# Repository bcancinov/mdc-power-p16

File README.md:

# mdc-power-p16
Modular Detector Controller Power 16V DC-DC Mezzanine Module

## Overview
12V input to 16V output DC-DC module, 0.5A nominal output, used as one of the `mdc-power-*` bias rails.
Designed for 2 MHz sync operation.
Mezzanine module.

## Power Stage
- Controller: `LT8350S` (`U1`)
  - 4-switch, single-inductor synchronous buck-boost controller (Silent Switcher 2 family).
  - Supports input above/below VOUT, suitable for regulated 16V from 12V input.
  - Silent Switcher 2 architecture for reduced EMI and cleaner switch-node behavior.
  - Single-inductor buck-boost topology simplifies power stage while handling input transients.
- Inductor: `L1` = `3.3uH`
  - Uses the XGL4020 shielded power inductor family (see `docs/xgl4020.pdf`).
  - Shielded construction to reduce radiated EMI and coupling into sensitive nodes.
  - Very low DCR family to reduce copper loss and improve efficiency.
  - Low AC loss construction optimized for high-frequency switching.

## Files
- Schematic: `power_p16.pdf`
- Simulation: `sim/` (LTspice and LTpowerCAD files used for loop and transient checks)

## Board Dimensions
- 44.8 mm x 41.5 mm

## Board Stackup
- 4-layer PCB

## CAD
- Designed using KiCad 9.

## Interface
- Control pins: `EN` (enable) and `PG` / `~PGOOD` (power good).
- Connector: `LSHM-140-04.0-L-DV-A-N-K-TR` (Samtec LSHM series) mezzanine for power and control signals.
  - Common pinout is shared across the 16V, -16V, 6V, and 3.3V variants.
  - Unused output rails are tied to GND on the specific module variant.

## Images
Layout:

3D view:

## License

This hardware design is licensed under the **Creative Commons Attribution-NonCommercial-ShareAlike 4.0 International License** (CC BY-NC-SA 4.0).

You are free to download, modify, and build upon this design for your own research or personal use, provided you give appropriate credit and share your modifications under the exact same license. **Commercial manufacturing or use of these designs is strictly prohibited without explicit permission.**

To view a copy of this license, visit [http://creativecommons.org/licenses/by-nc-sa/4.0/](http://creativecommons.org/licenses/by-nc-sa/4.0/) or see the `LICENSE` file in this repository.

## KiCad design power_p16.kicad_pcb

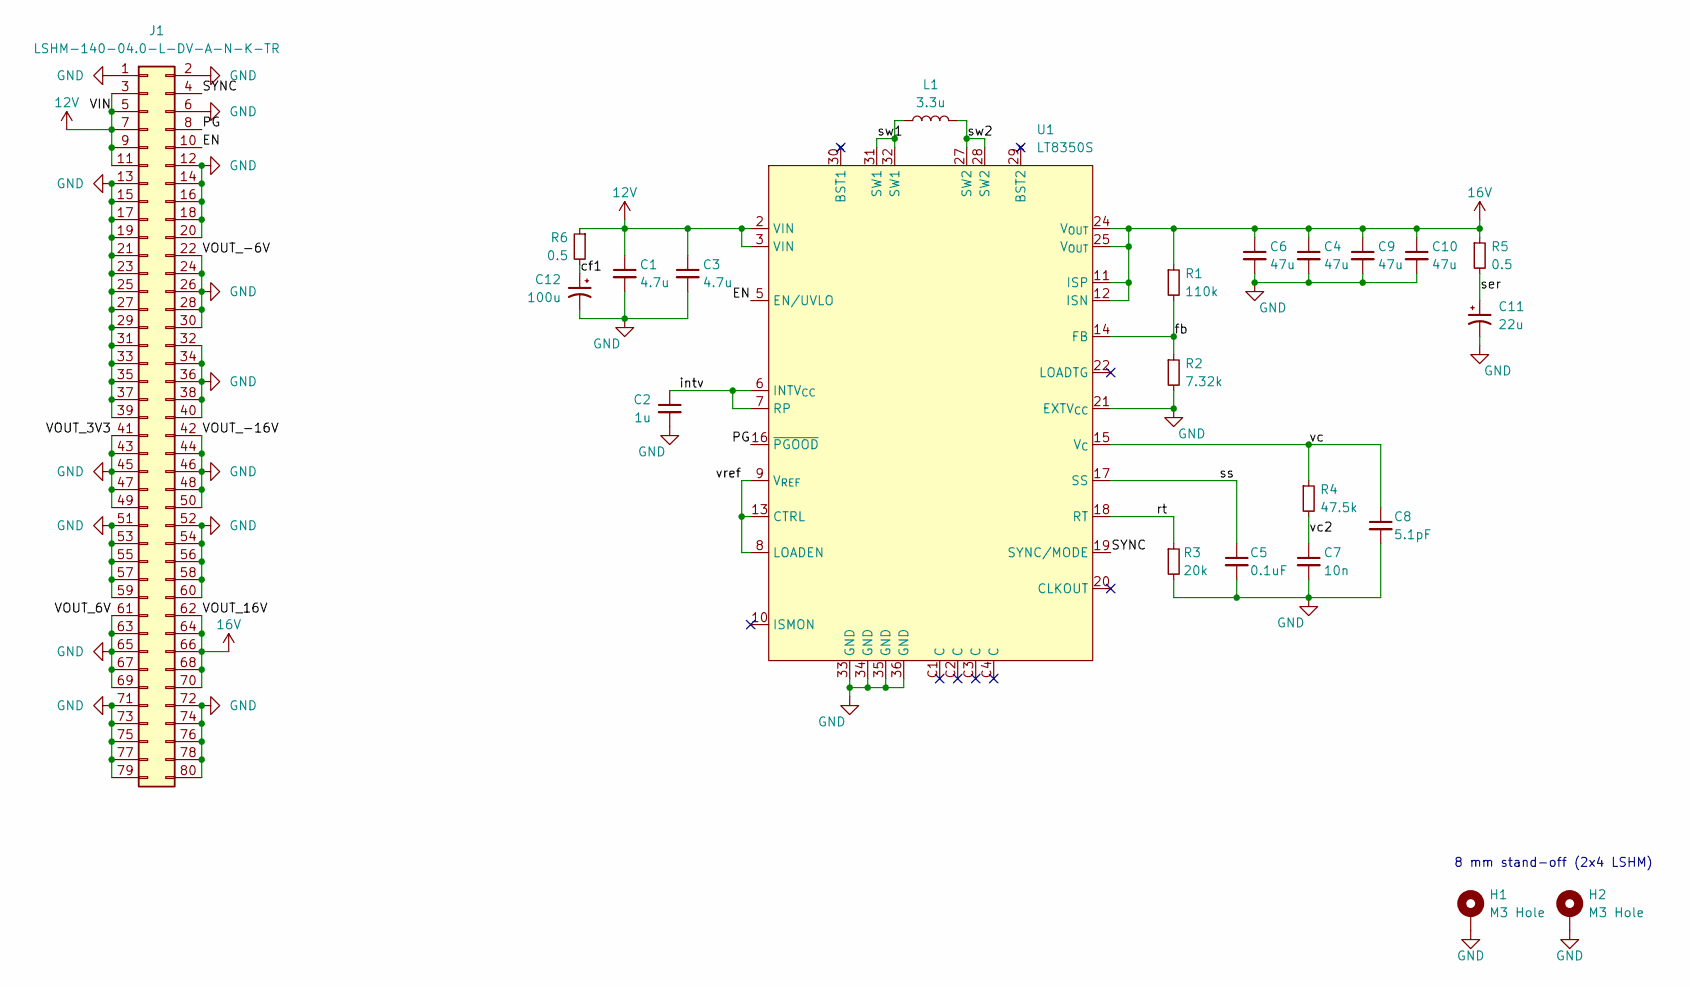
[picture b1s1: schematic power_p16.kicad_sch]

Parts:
C1, C3: 4.7u; C_1210_3225Metric; MPN GCM32ER71H475KA55K
C2: 1u; C_0603_1608Metric; MPN GCM188R71E105KA64D
C4, C6, C9, C10: 47u; C_1210_3225Metric; MPN TMK325ABJ476MM-P
C5: 0.1uF; C_0402_1005Metric; MPN GCM155R71H104KE02J
C7: 10n; C_0603_1608Metric; MPN GRT1885C1E103FA02D
C8: 5.1pF; C_0603_1608Metric; MPN CBR06C519C5GACAUTO
C11: 22u; CP_EIA-7343-20_Kemet-V; MPN T521V226M025ATE040
C12: 100u; T521X; MPN T521X107M025ATE060
H1, H2: M3 Hole; MountingHole_3.2mm_M3_Pad_Via
J1: LSHM-140-04.0-L-DV-A-N-K-TR; SAMTEC_LSHM-140-04.0-L-DV-A-N-K-TR; MPN LSHM-140-04.0-L-DV-A-N-K-TR
L1: 3.3u; XGL4020; MPN XGL4020-332MEC
R1: 110k; R_0603_1608Metric; MPN ERA-3AEB114V
R2: 7.32k; R_0603_1608Metric; MPN ERA-3AEB7321V
R3: 20k; R_0603_1608Metric; MPN CRCW060320K0FKEA
R4: 47.5k; R_0603_1608Metric; MPN CRCW060347K5FKEA
R5, R6: 0.5; R_0603_1608Metric; MPN RCWE0603R500FKEA
U1: LT8350S; MPN LT8350SAV#PBF

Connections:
12V: C1.1, C3.1, J1.3, J1.5, J1.7, J1.9, J1.11, R6.1, U1.2 (VIN), U1.3 (VIN)
16V: C4.1, C6.1, C9.1, C10.1, J1.62, J1.64, J1.66, J1.68, J1.70, R1.1, R5.1, U1.11 (ISP), U1.12 (ISN), U1.24 (V_{OUT}), U1.25 (V_{OUT})
/EN: J1.10, U1.5 (EN/UVLO)
/PG: J1.8, U1.16 (~PGOOD)
/SYNC: J1.4, U1.19 (SYNC/MODE)
/cf1: C12.1, R6.2
/fb: R1.2, R2.1, U1.14 (FB)
/intv: C2.1, U1.6 (INTV_{CC}), U1.7 (RP)
/rt: R3.1, U1.18 (RT)
/ser: C11.1, R5.2
/ss: C5.1, U1.17 (SS)
/sw1: L1.2, U1.31 (SW1), U1.32 (SW1)
/sw2: L1.1, U1.27 (SW2), U1.28 (SW2)
/vc: C8.1, R4.1, U1.15 (V_{C})
/vc2: C7.1, R4.2
/vref: U1.8 (LOADEN), U1.9 (V_{REF}), U1.13 (CTRL)
GND: C1.2, C2.2, C3.2, C4.2, C5.2, C6.2, C7.2, C8.2, C9.2, C10.2, C11.2, C12.2, H1.1, H2.1, J1.1, J1.2, J1.6, J1.12, J1.13, J1.14, J1.15, J1.16, J1.17, J1.18, J1.19, J1.20, J1.21, J1.22, J1.23, J1.24, J1.25, J1.26, J1.27, J1.28, J1.29, J1.30, J1.31, J1.32, J1.33, J1.34, J1.35, J1.36, J1.37, J1.38, J1.39, J1.40, J1.41, J1.42, J1.43, J1.44, J1.45, J1.46, J1.47, J1.48, J1.49, J1.50, J1.51, J1.52, J1.53, J1.54, J1.55, J1.56, J1.57, J1.58, J1.59, J1.60, J1.61, J1.63, J1.65, J1.67, J1.69, J1.71, J1.72, J1.73, J1.74, J1.75, J1.76, J1.77, J1.78, J1.79, J1.80, R2.2, R3.2, U1.21 (EXTV_{CC}), U1.33 (GND), U1.34 (GND), U1.35 (GND), U1.36 (GND)

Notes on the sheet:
8 mm stand-off (2x4 LSHM)

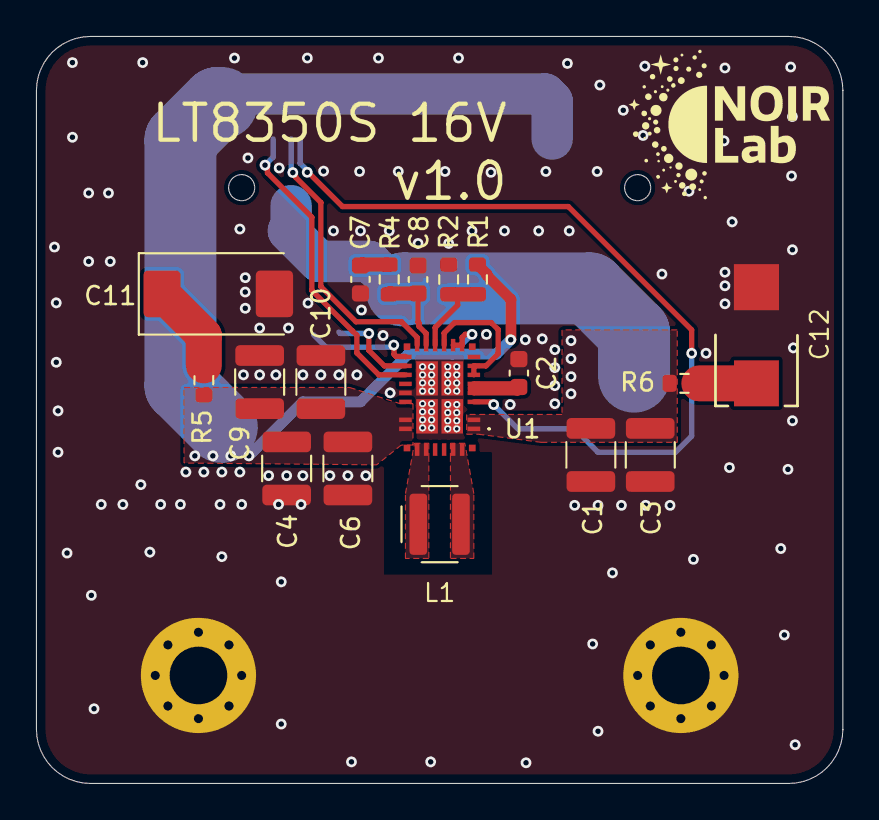
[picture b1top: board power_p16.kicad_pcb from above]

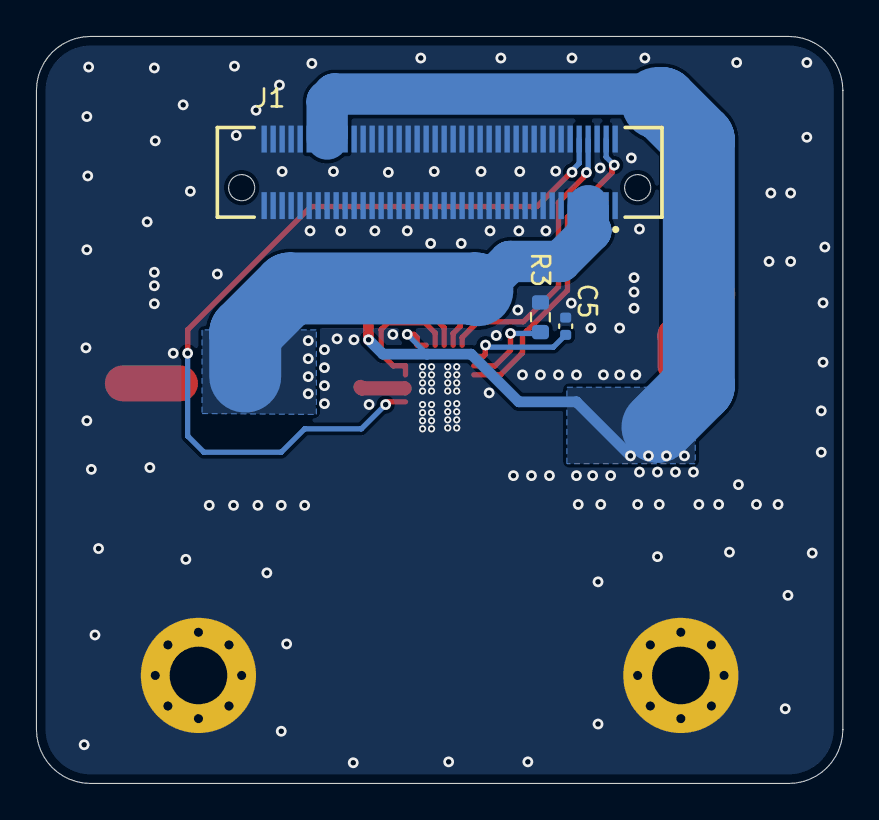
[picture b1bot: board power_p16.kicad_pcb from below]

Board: 4 copper layers, 44.8 x 41.5 mm, 23 parts (3 on the bottom side), 17 nets.

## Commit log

2026-02-06 update readme and docs
2026-02-17 Add input RC snubber
2026-03-18 update feedback resistor to thin film
2026-03-27 add license
